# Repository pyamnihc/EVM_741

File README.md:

# EVM_741

The schematic and pcb are "a faithful and functional transistor-scale replica of the μA741 op-amp integrated circuit" from [a kit by Evil Mad Scientist](https://shop.evilmadscientist.com/productsmenu/923)

The schematic simulates the 741 op-amp as a buffer

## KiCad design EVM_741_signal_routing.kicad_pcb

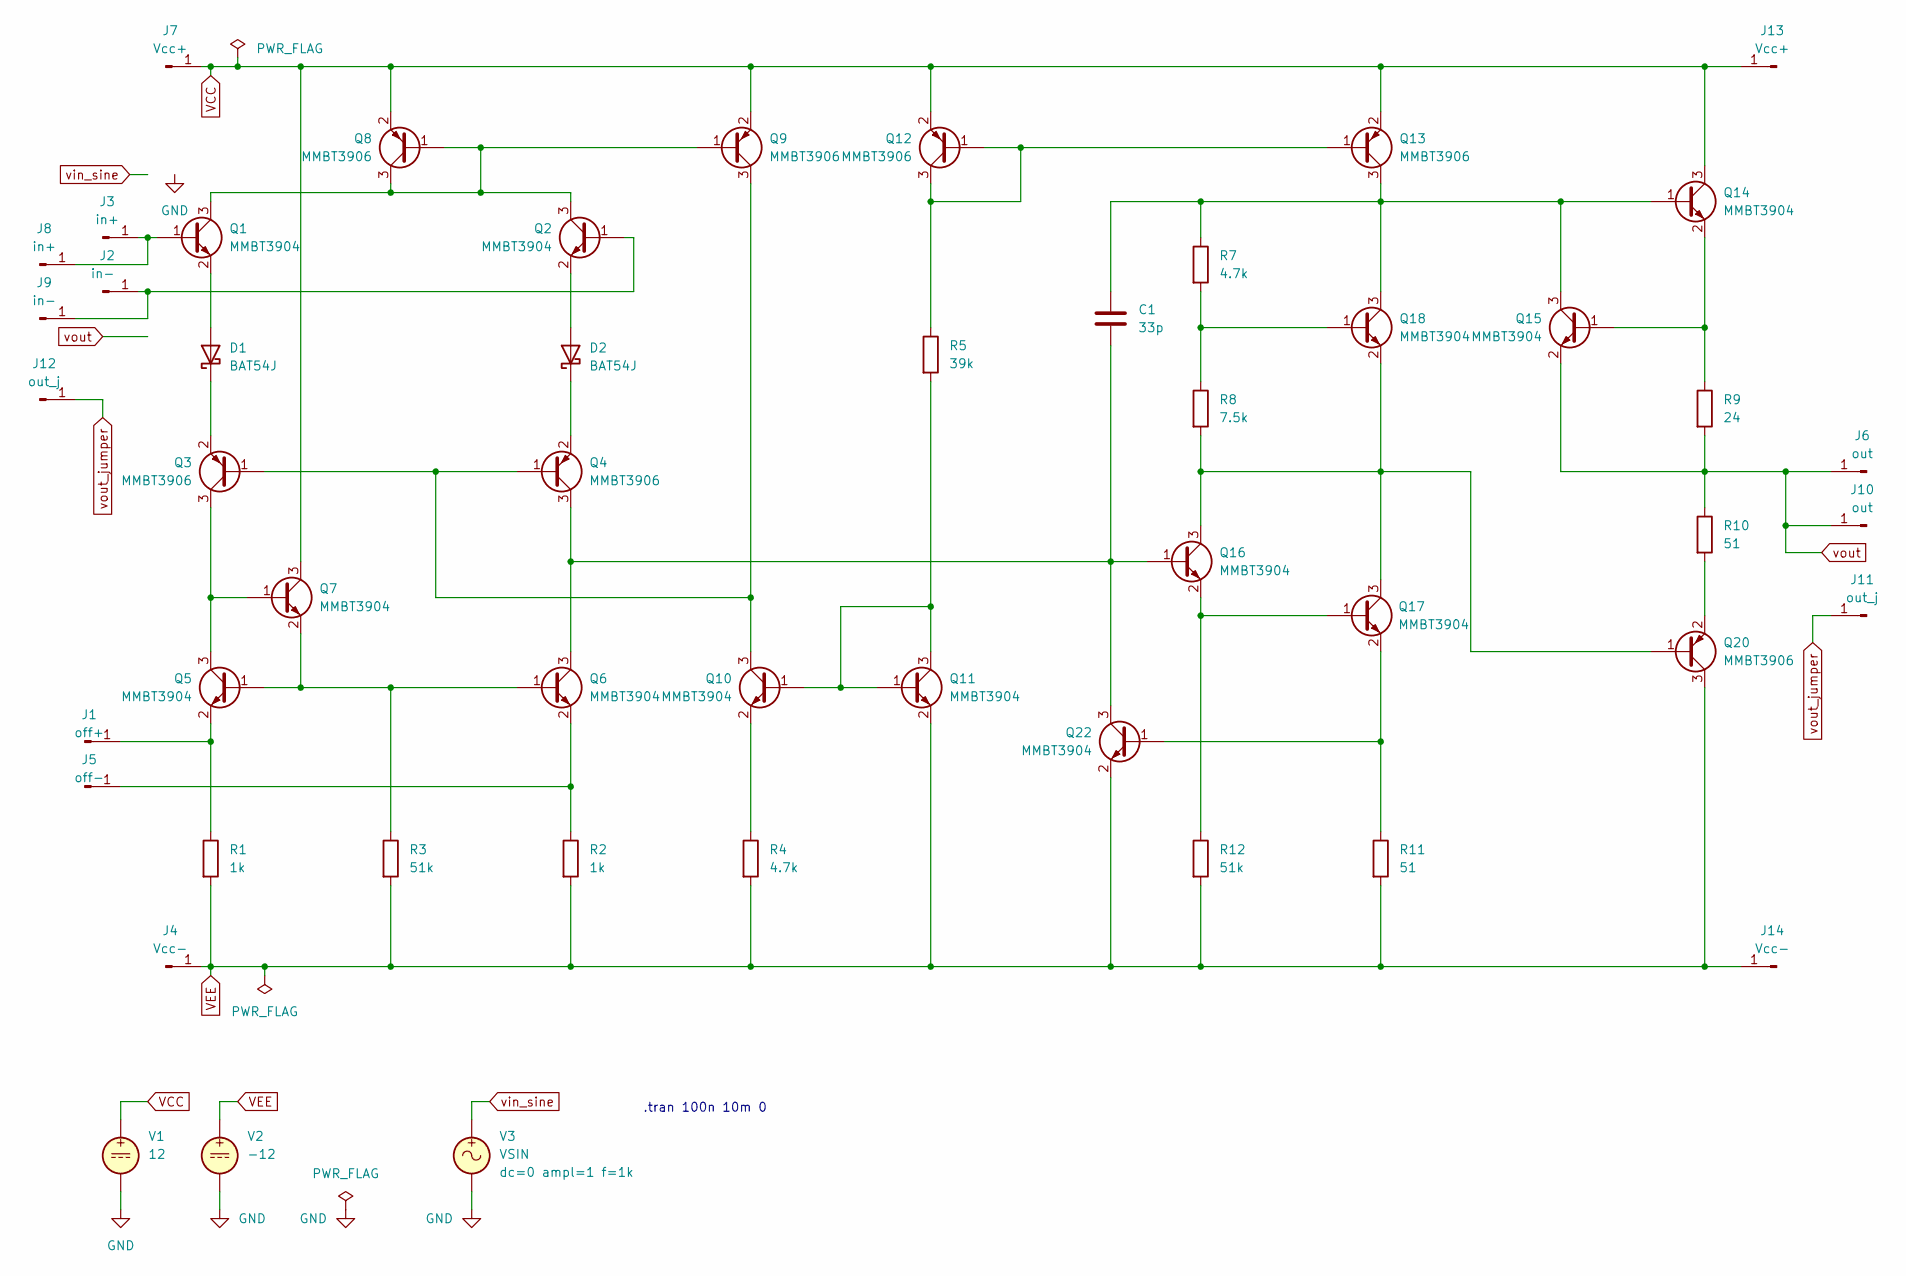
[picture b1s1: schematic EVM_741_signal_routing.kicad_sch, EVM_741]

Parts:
C1: 33p; C_1206_3216Metric_Pad1.33x1.80mm_HandSolder
D1, D2: BAT54J; D_SOD-323F
J1: off+; PinHeader_1x01_P2.54mm_Vertical
J2: in-; PinHeader_1x01_P2.54mm_Vertical
J3: in+; PinHeader_1x01_P2.54mm_Vertical
J4: Vcc-; PinSocket_1x01_P2.54mm_Vertical
J5: off-; PinHeader_1x01_P2.54mm_Vertical
J6: out; PinHeader_1x01_P2.54mm_Vertical
J7: Vcc+; PinSocket_1x01_P2.54mm_Vertical
J8: in+; PinSocket_1x01_P2.54mm_Vertical
J9: in-; PinSocket_1x01_P2.54mm_Vertical
J10: out; PinSocket_1x01_P2.54mm_Vertical
J11, J12: out_j; PinSocket_1x01_P2.54mm_Vertical
J13: Vcc+; PinHeader_1x01_P2.54mm_Vertical
J14: Vcc-; PinHeader_1x01_P2.54mm_Vertical
Q1, Q2, Q5, Q6, Q7, Q10, Q11, Q14, Q15, Q16, Q17, Q18, Q22: MMBT3904; SOT-23
Q3, Q4, Q8, Q9, Q12, Q13, Q20: MMBT3906; SOT-23
R1, R2: 1k; R_1206_3216Metric_Pad1.30x1.75mm_HandSolder
R3, R12: 51k; R_1206_3216Metric_Pad1.30x1.75mm_HandSolder
R4, R7: 4.7k; R_1206_3216Metric_Pad1.30x1.75mm_HandSolder
R5: 39k; R_1206_3216Metric_Pad1.30x1.75mm_HandSolder
R8: 7.5k; R_1206_3216Metric_Pad1.30x1.75mm_HandSolder
R9: 24; R_1206_3216Metric_Pad1.30x1.75mm_HandSolder
R10, R11: 51; R_1206_3216Metric_Pad1.30x1.75mm_HandSolder
V1: 12
V2: -12
V3: VSIN

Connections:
unnamed: D1.2 (A), Q1.2 (E)
unnamed: D1.1 (K), Q3.2 (E)
unnamed: D2.2 (A), Q2.2 (E)
unnamed: D2.1 (K), Q4.2 (E)
unnamed: J1.1, Q5.2 (E), R1.1
unnamed: J2.1, J9.1, Q2.1 (B)
unnamed: J3.1, J8.1, Q1.1 (B)
unnamed: J5.1, Q6.2 (E), R2.1
unnamed: Q1.3 (C), Q2.3 (C), Q8.1 (B), Q8.3 (C), Q9.1 (B)
unnamed: Q3.3 (C), Q5.3 (C), Q7.1 (B)
unnamed: Q5.1 (B), Q6.1 (B), Q7.2 (E), R3.1
unnamed: Q10.1 (B), Q11.1 (B), Q11.3 (C), R5.2
unnamed: Q3.1 (B), Q4.1 (B), Q9.3 (C), Q10.3 (C)
unnamed: Q10.2 (E), R4.1
unnamed: Q12.1 (B), Q12.3 (C), Q13.1 (B), R5.1
unnamed: C1.1, Q13.3 (C), Q14.1 (B), Q15.3 (C), Q18.3 (C), R7.1
unnamed: Q14.2 (E), Q15.1 (B), R9.1
unnamed: C1.2, Q4.3 (C), Q6.3 (C), Q16.1 (B), Q22.3 (C)
unnamed: Q16.3 (C), Q17.3 (C), Q18.2 (E), Q20.1 (B), R8.2
unnamed: Q16.2 (E), Q17.1 (B), R12.1
unnamed: Q17.2 (E), Q22.1 (B), R11.1
unnamed: Q18.1 (B), R7.2, R8.1
unnamed: Q20.2 (E), R10.2
unnamed: V1.2, V2.2, V3.2
VCC: J7.1, J13.1, Q7.3 (C), Q8.2 (E), Q9.2 (E), Q12.2 (E), Q13.2 (E), Q14.3 (C), V1.1
VEE: J4.1, J14.1, Q11.2 (E), Q20.3 (C), Q22.2 (E), R1.2, R2.2, R3.2, R4.2, R11.2, R12.2, V2.1
vout: J6.1, J10.1, Q15.2 (E), R9.2, R10.1
vout_jumper: J11.1, J12.1

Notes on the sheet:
.tran 100n 10m 0

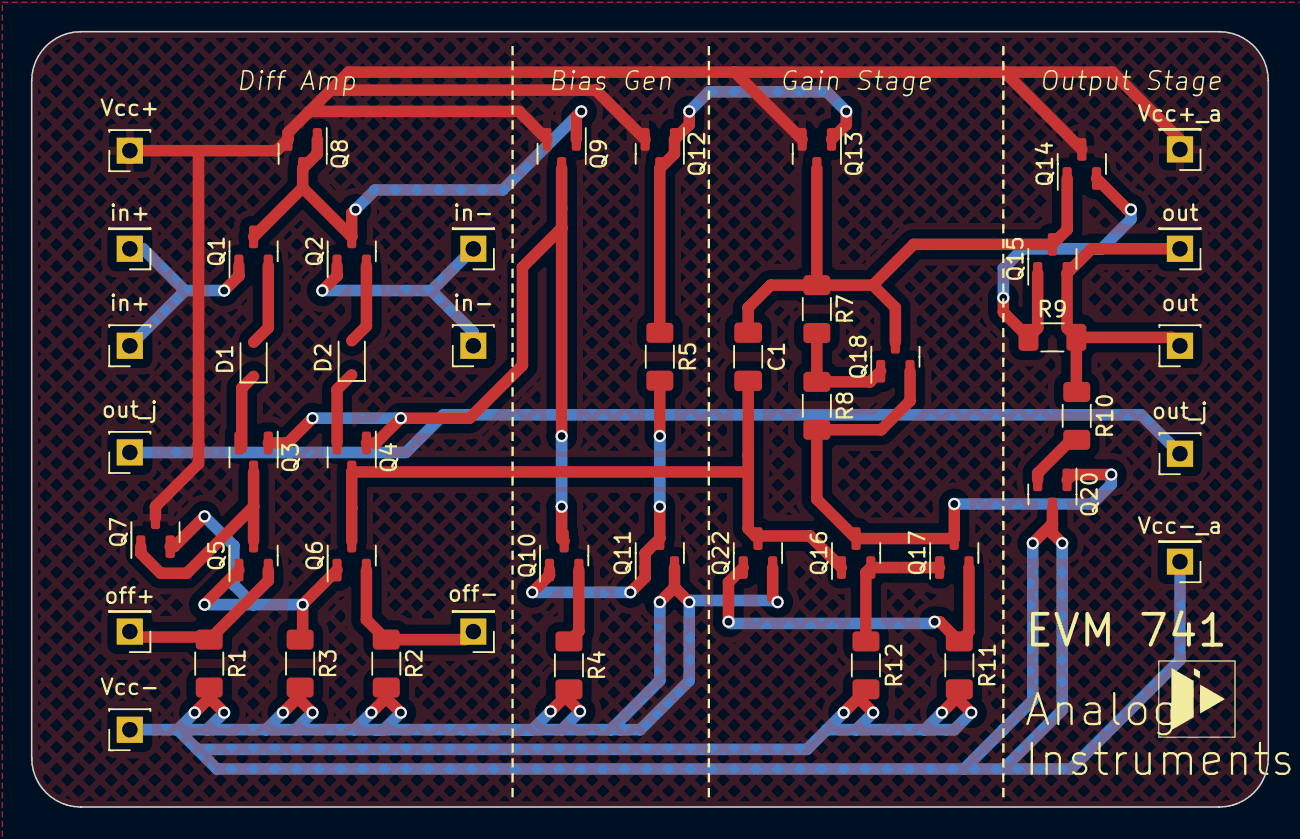
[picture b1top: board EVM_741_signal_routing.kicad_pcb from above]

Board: 2 copper layers, 80.0 x 50.2 mm, 48 parts (0 on the bottom side), 27 nets.

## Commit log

2023-05-19 added spice sim lib
2023-05-19 fixed lib paths
2023-05-20 fixed fill zones
2023-05-20 add README.md
2023-05-20 pruned unnecessary files
2023-05-21 fixed silkscreen
